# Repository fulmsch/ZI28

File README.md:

# ZI-28: An Expandable Z80 Microcomputer

The ZI-28 is my attempt at developing a Z80 based microcomputer.
The main goals were to have a system that's about as usable as
a personal computer of the 80s and easily expandable with additional hardware.

The project is still very much a work in progress. Both the hardware and the
OS are functional, but many planned features have yet to be implemented.

If you want to try out yourself what using the ZI-28 feels like, you can do so
with the included emulator. See the quick start guide for instructions.

## Prerequisites

It is assumed that you have a standard Linux develompent environment
(gcc, make, etc.) setup already. To build the emulator, you also need Lua 5.3.

The Z80 software requires Z88DK v1.99B in order to be built. Make sure to have
all of the Z88DK binaries in your path. You don't need to worry about the ZCCCFG
environment variable; it gets set automatically by the Makefiles.

The emulator creates a pseudoterminal to simulate the serial connection of the
real computer. To access it, you will need a terminal emulator. For the easiest
experience, picocom should be installed, though you can also use any other one.

## Quick start guide

Ensure that you have all prerequisites installed. Type `make` to build the
entire project. You might be promted for your password to mount the filesystem
image. If the build completed successfully, type `make run`. This will open
the emulator with the newly built ROM- and SD-images and start picocom in your
current terminal window. Click the `continue`-button of the emulator to start
the system.

## Contents of this repository

* **emulator**: Based on libz80 by Gabriel Gambetta, this emulator simulates the
  Z80 processor and all the periphery of the ZI-28. It also includes some
  debugging features.
* **include**: Header files for the C library. These also form the interface to
  the operating system.
* **lib**: Library for compiling C code. Mostly copied from z88dk, but modified
  and expanded for the particularities of the ZI-28.
* **system**: Everything that's part of the machine itself, most notably the
  ROM-based operating system.
* **tools**: Utilities supporting the project.
* **user**: Various programs for the system.

## License

All code original to the ZI-28 project is licensed under the terms of the
GNU General Public License v3.0.

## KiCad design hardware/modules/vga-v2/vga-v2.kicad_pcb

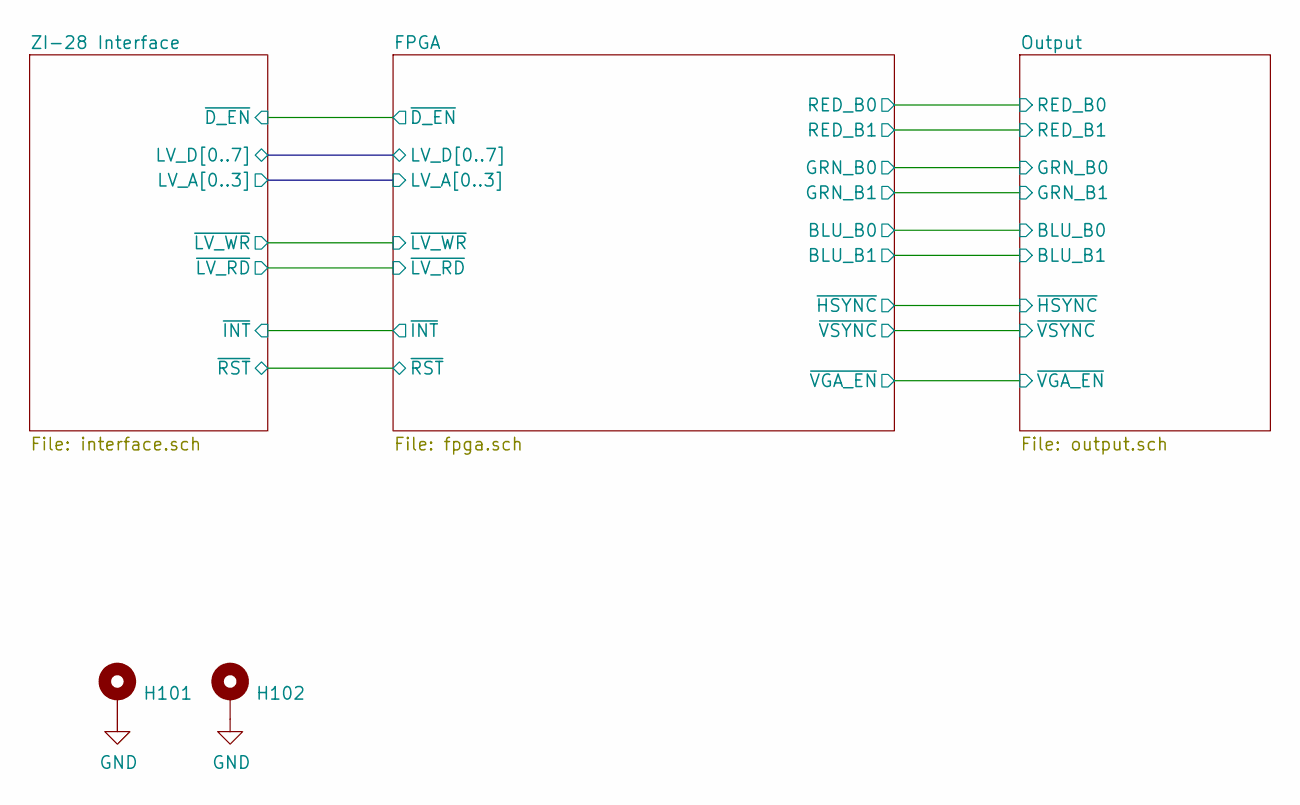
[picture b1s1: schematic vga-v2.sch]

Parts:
H101, H102: MountingHole_Pad; MountingHole_3.2mm_M3_Pad

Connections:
GND: H101.1, H102.1; also elsewhere on the board

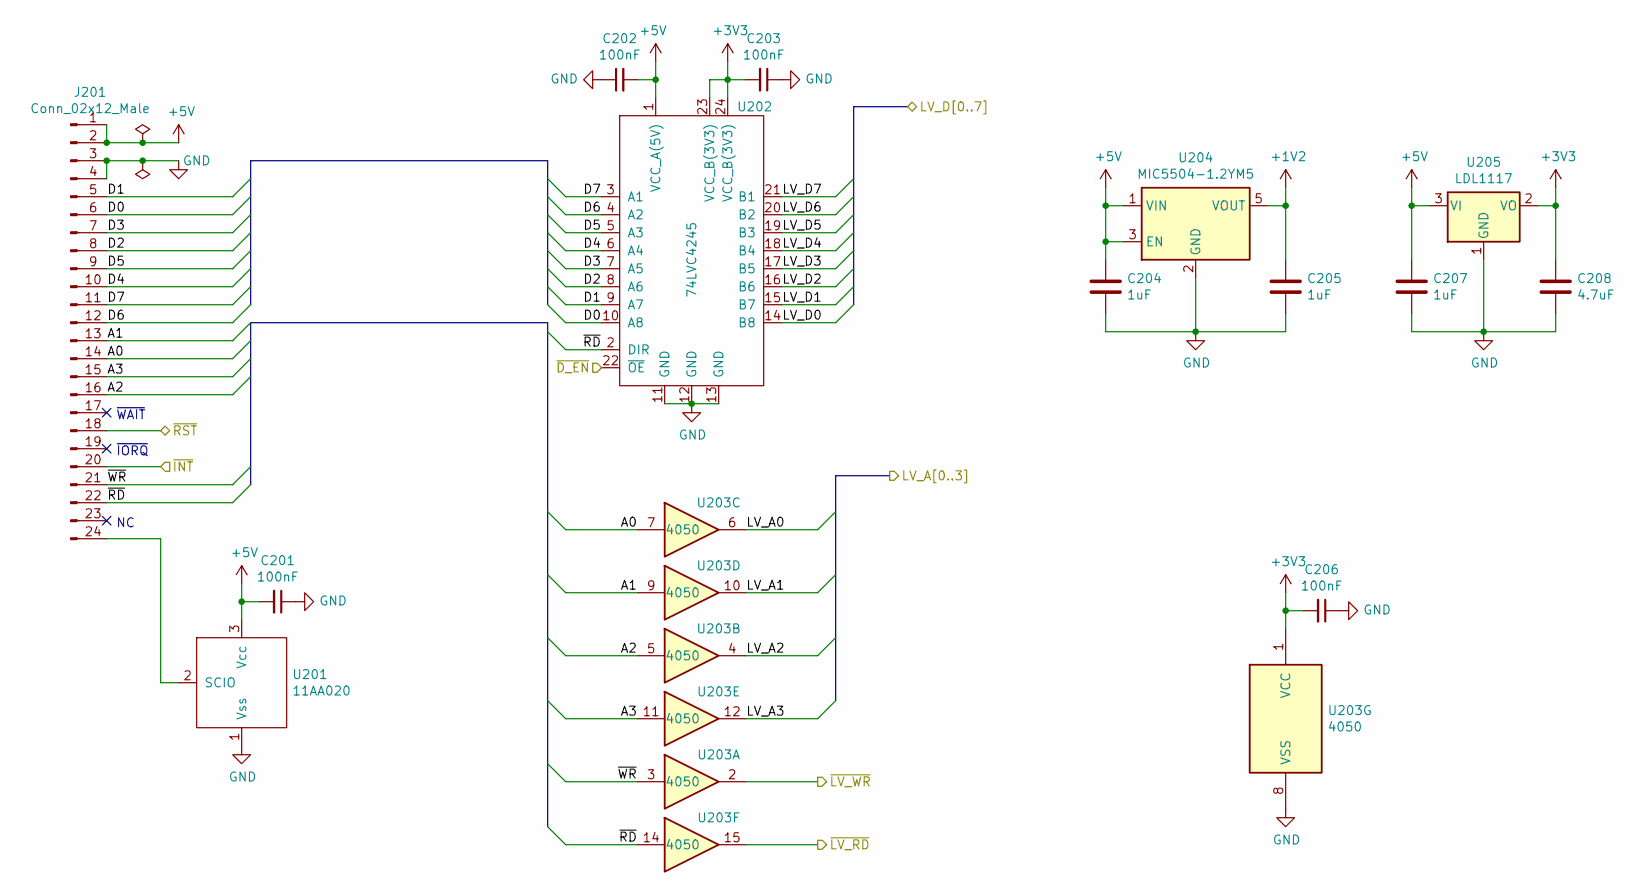
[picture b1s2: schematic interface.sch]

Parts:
C201, C202, C203, C206: 100nF; C_0805_2012Metric_Pad1.15x1.40mm_HandSolder
C204, C205, C207: 1uF; C_0805_2012Metric_Pad1.15x1.40mm_HandSolder
C208: 4.7uF; C_0805_2012Metric_Pad1.15x1.40mm_HandSolder
J201: Conn_02x12_Male; PinHeader_2x12_P2.54mm_Horizontal
U201: 11AA020; TO-92
U202: 74LVC4245; SOIC-24W_7.5x15.4mm_P1.27mm
U203: 4050; SOIC-16W_7.5x10.3mm_P1.27mm
U204: MIC5504-1.2YM5; SOT-23-5
U205: LDL1117; SOT-223-3_TabPin2

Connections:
+1V2: C205.1, U204.5 (VOUT); also elsewhere on the board
+3V3: C203.2, C206.2, C208.1, U202.23 (VCC_B(3V3)), U202.24 (VCC_B(3V3)), U203.1 (VCC), U205.2 (VO); also elsewhere on the board
+5V: C201.2, C202.2, C204.1, C207.1, J201.1, J201.2, U201.3 (Vcc), U202.1 (VCC_A(5V)), U204.1 (VIN), U204.3 (EN), U205.3 (VI)
/FPGA/LV_A0: U203.6; also elsewhere on the board
/FPGA/LV_A1: U203.10; also elsewhere on the board
/FPGA/LV_A2: U203.4; also elsewhere on the board
/FPGA/LV_A3: U203.12; also elsewhere on the board
/FPGA/LV_D0: U202.14 (B8); also elsewhere on the board
/FPGA/LV_D1: U202.15 (B7); also elsewhere on the board
/FPGA/LV_D2: U202.16 (B6); also elsewhere on the board
/FPGA/LV_D3: U202.17 (B5); also elsewhere on the board
/FPGA/LV_D4: U202.18 (B4); also elsewhere on the board
/FPGA/LV_D5: U202.19 (B3); also elsewhere on the board
/FPGA/LV_D6: U202.20 (B2); also elsewhere on the board
/FPGA/LV_D7: U202.21 (B1); also elsewhere on the board
/FPGA/~D_EN: U202.22 (~OE); also elsewhere on the board
/FPGA/~INT: J201.20; also elsewhere on the board
/FPGA/~LV_RD: U203.15; also elsewhere on the board
/FPGA/~LV_WR: U203.2; also elsewhere on the board
/FPGA/~RST: J201.18; also elsewhere on the board
/ZI-28 Interface/A0: J201.14, U203.7
/ZI-28 Interface/A1: J201.13, U203.9
/ZI-28 Interface/A2: J201.16, U203.5
/ZI-28 Interface/A3: J201.15, U203.11
/ZI-28 Interface/D0: J201.6, U202.10 (A8)
/ZI-28 Interface/D1: J201.5, U202.9 (A7)
/ZI-28 Interface/D2: J201.8, U202.8 (A6)
/ZI-28 Interface/D3: J201.7, U202.7 (A5)
/ZI-28 Interface/D4: J201.10, U202.6 (A4)
/ZI-28 Interface/D5: J201.9, U202.5 (A3)
/ZI-28 Interface/D6: J201.12, U202.4 (A2)
/ZI-28 Interface/D7: J201.11, U202.3 (A1)
/ZI-28 Interface/~RD: J201.22, U202.2 (DIR), U203.14
/ZI-28 Interface/~WR: J201.21, U203.3
GND: C201.1, C202.1, C203.1, C204.2, C205.2, C206.1, C207.2, C208.2, J201.3, J201.4, U201.1 (Vss), U202.11 (GND), U202.12 (GND), U202.13 (GND), U203.8 (VSS), U204.2 (GND), U205.1 (GND); also elsewhere on the board
unnamed: J201.24, U201.2 (SCIO)

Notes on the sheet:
~WAIT
~IORQ

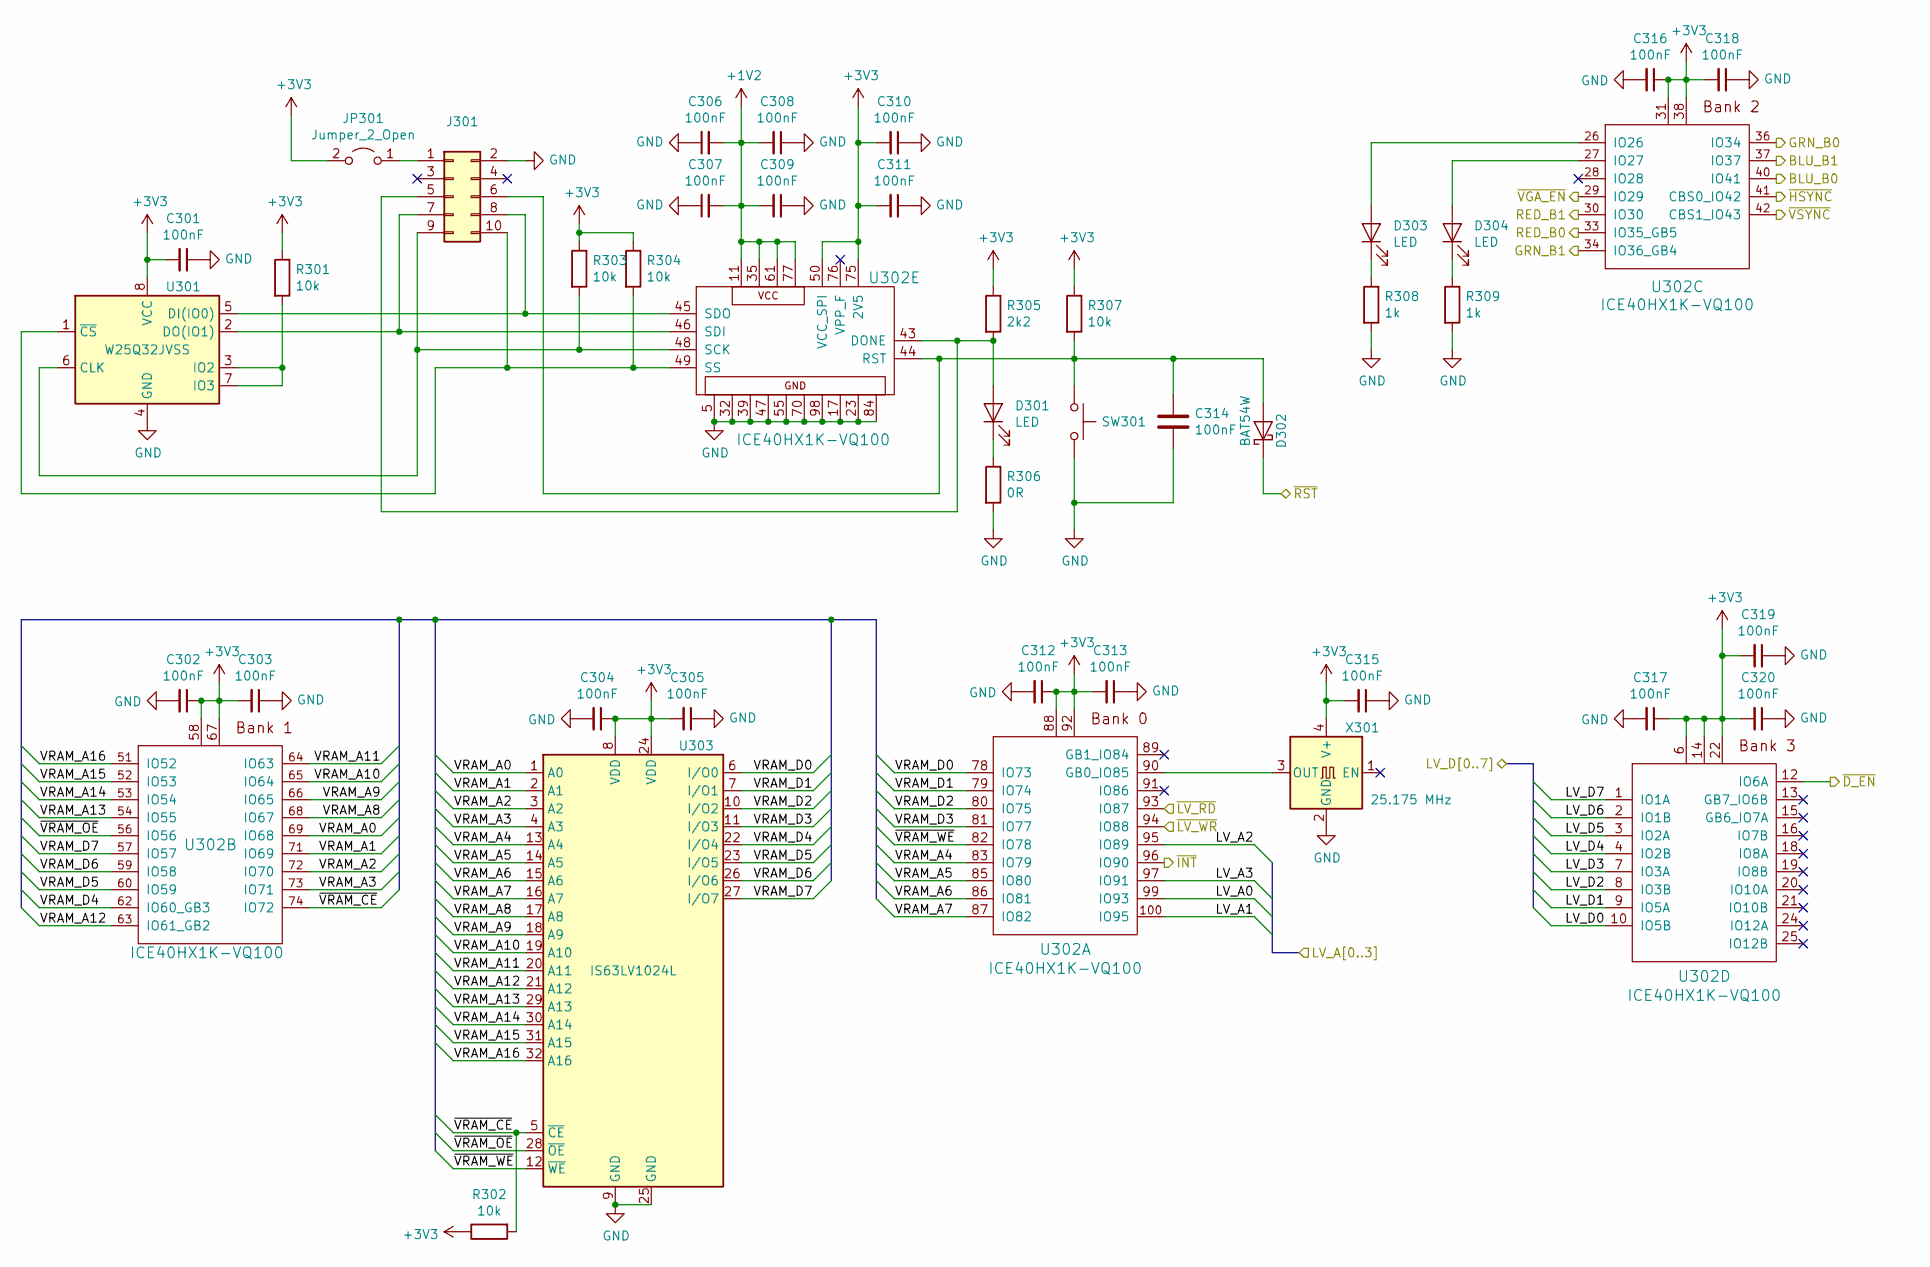
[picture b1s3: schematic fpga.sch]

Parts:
C301, C302, C303, C304, C305, C306, C307, C308, C309, C310, C311, C312, C313, C314, C315, C316, C317, C318, C319, C320: 100nF; C_0805_2012Metric_Pad1.15x1.40mm_HandSolder
D301, D303, D304: LED; LED_D3.0mm
D302: BAT54W; D_SOD-123
J301: Conn_02x05_Odd_Even; IDC-Header_2x05_P2.54mm_Vertical
JP301: Jumper_2_Open; PinHeader_1x02_P2.54mm_Vertical
R301, R302, R303, R304, R307: 10k; R_0805_2012Metric_Pad1.15x1.40mm_HandSolder
R305: 2k2; R_0805_2012Metric_Pad1.15x1.40mm_HandSolder
R306: 0R; R_0805_2012Metric_Pad1.15x1.40mm_HandSolder
R308, R309: 1k; R_0805_2012Metric_Pad1.15x1.40mm_HandSolder
SW301: SW_Push; SW_PUSH_6mm_H5mm
U301: W25Q32JVSS; DIP-8_W7.62mm_Socket
U302: ICE40HX1K-VQ100; VQFP-100_14x14mm_P0.5mm
U303: IS63LV1024L; TSOP-II-32_21.0x10.2mm_P1.27mm
X301: 25.175 MHz; Oscillator_SMD_Abracon_ASV-4Pin_7.0x5.1mm_HandSoldering

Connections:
+1V2: C306.2, C307.2, C308.2, C309.2, U302.11, U302.35, U302.61, U302.77; also elsewhere on the board
+3V3: C301.2, C302.1, C303.2, C304.1, C305.2, C310.2, C311.2, C312.1, C313.2, C315.2, C316.1, C317.1, C318.2, C319.2, C320.2, JP301.2 (B), R301.1, R302.1, R303.1, R304.1, R305.1, R307.1, U301.8 (VCC), U302.6, U302.14, U302.22, U302.31, U302.38, U302.50 (VCC_SPI), U302.58, U302.67, U302.75 (2V5), U302.88, U302.92, U303.8 (VDD), U303.24 (VDD), X301.4 (V+); also elsewhere on the board
/FPGA/BLU_B0: U302.40 (IO41); also elsewhere on the board
/FPGA/BLU_B1: U302.37 (IO37); also elsewhere on the board
/FPGA/GRN_B0: U302.36 (IO34); also elsewhere on the board
/FPGA/GRN_B1: U302.34 (IO36_GB4); also elsewhere on the board
/FPGA/LV_A0: U302.99 (IO93); also elsewhere on the board
/FPGA/LV_A1: U302.100 (IO95); also elsewhere on the board
/FPGA/LV_A2: U302.95 (IO89); also elsewhere on the board
/FPGA/LV_A3: U302.97 (IO91); also elsewhere on the board
/FPGA/LV_D0: U302.10 (IO5B); also elsewhere on the board
/FPGA/LV_D1: U302.9 (IO5A); also elsewhere on the board
/FPGA/LV_D2: U302.8 (IO3B); also elsewhere on the board
/FPGA/LV_D3: U302.7 (IO3A); also elsewhere on the board
/FPGA/LV_D4: U302.4 (IO2B); also elsewhere on the board
/FPGA/LV_D5: U302.3 (IO2A); also elsewhere on the board
/FPGA/LV_D6: U302.2 (IO1B); also elsewhere on the board
/FPGA/LV_D7: U302.1 (IO1A); also elsewhere on the board
/FPGA/RED_B0: U302.33 (IO35_GB5); also elsewhere on the board
/FPGA/RED_B1: U302.30 (IO30); also elsewhere on the board
/FPGA/VRAM_A0: U302.69 (IO68), U303.1 (A0)
/FPGA/VRAM_A1: U302.71 (IO69), U303.2 (A1)
/FPGA/VRAM_A2: U302.72 (IO70), U303.3 (A2)
/FPGA/VRAM_A3: U302.73 (IO71), U303.4 (A3)
/FPGA/VRAM_A4: U302.83 (IO79), U303.13 (A4)
/FPGA/VRAM_A5: U302.85 (IO80), U303.14 (A5)
/FPGA/VRAM_A6: U302.86 (IO81), U303.15 (A6)
/FPGA/VRAM_A7: U302.87 (IO82), U303.16 (A7)
/FPGA/VRAM_A8: U302.68 (IO67), U303.17 (A8)
/FPGA/VRAM_A9: U302.66 (IO65), U303.18 (A9)
/FPGA/VRAM_A10: U302.65 (IO64), U303.19 (A10)
/FPGA/VRAM_A11: U302.64 (IO63), U303.20 (A11)
/FPGA/VRAM_A12: U302.63 (IO61_GB2), U303.21 (A12)
/FPGA/VRAM_A13: U302.54 (IO55), U303.29 (A13)
/FPGA/VRAM_A14: U302.53 (IO54), U303.30 (A14)
/FPGA/VRAM_A15: U302.52 (IO53), U303.31 (A15)
/FPGA/VRAM_A16: U302.51 (IO52), U303.32 (A16)
/FPGA/VRAM_D0: U302.78 (IO73), U303.6 (I/O0)
/FPGA/VRAM_D1: U302.79 (IO74), U303.7 (I/O1)
/FPGA/VRAM_D2: U302.80 (IO75), U303.10 (I/O2)
/FPGA/VRAM_D3: U302.81 (IO77), U303.11 (I/O3)
/FPGA/VRAM_D4: U302.62 (IO60_GB3), U303.22 (I/O4)
/FPGA/VRAM_D5: U302.60 (IO59), U303.23 (I/O5)
/FPGA/VRAM_D6: U302.59 (IO58), U303.26 (I/O6)
/FPGA/VRAM_D7: U302.57 (IO57), U303.27 (I/O7)
/FPGA/~D_EN: U302.12 (IO6A); also elsewhere on the board
/FPGA/~HSYNC: U302.41 (CBS0_IO42); also elsewhere on the board
/FPGA/~INT: U302.96 (IO90); also elsewhere on the board
/FPGA/~LV_RD: U302.93 (IO87); also elsewhere on the board
/FPGA/~LV_WR: U302.94 (IO88); also elsewhere on the board
/FPGA/~RST: D302.1 (K); also elsewhere on the board
/FPGA/~VGA_EN: U302.29 (IO29); also elsewhere on the board
/FPGA/~VRAM_CE: R302.2, U302.74 (IO72), U303.5 (~CE)
/FPGA/~VRAM_OE: U302.56 (IO56), U303.28 (~OE)
/FPGA/~VRAM_WE: U302.82 (IO78), U303.12 (~WE)
/FPGA/~VSYNC: U302.42 (CBS1_IO43); also elsewhere on the board
GND: C301.1, C302.2, C303.1, C304.2, C305.1, C306.1, C307.1, C308.1, C309.1, C310.1, C311.1, C312.2, C313.1, C314.2, C315.1, C316.2, C317.2, C318.1, C319.1, C320.1, J301.2, R306.2, R308.2, R309.2, SW301.2, U301.4 (GND), U302.5, U302.17, U302.23, U302.32, U302.39, U302.47, U302.55, U302.70, U302.84, U302.98, U303.9 (GND), U303.25 (GND), X301.2 (GND); also elsewhere on the board
unnamed: C314.1, D302.2 (A), J301.6, R307.2, SW301.1, U302.44 (RST)
unnamed: D301.1 (K), R306.1
unnamed: D301.2 (A), J301.5, R305.2, U302.43 (DONE)
unnamed: D303.1 (K), R308.1
unnamed: D303.2 (A), U302.26 (IO26)
unnamed: D304.1 (K), R309.1
unnamed: D304.2 (A), U302.27 (IO27)
unnamed: J301.1, JP301.1 (A)
unnamed: J301.7, U301.2 (DO(IO1)), U302.46 (SDI)
unnamed: J301.8, U301.5 (DI(IO0)), U302.45 (SDO)
unnamed: J301.9, R303.2, U301.6 (CLK), U302.48 (SCK)
unnamed: J301.10, R304.2, U301.1 (~CS), U302.49 (SS)
unnamed: R301.2, U301.3 (IO2), U301.7 (IO3)
unnamed: U302.90 (GB0_IO85), X301.3 (OUT)

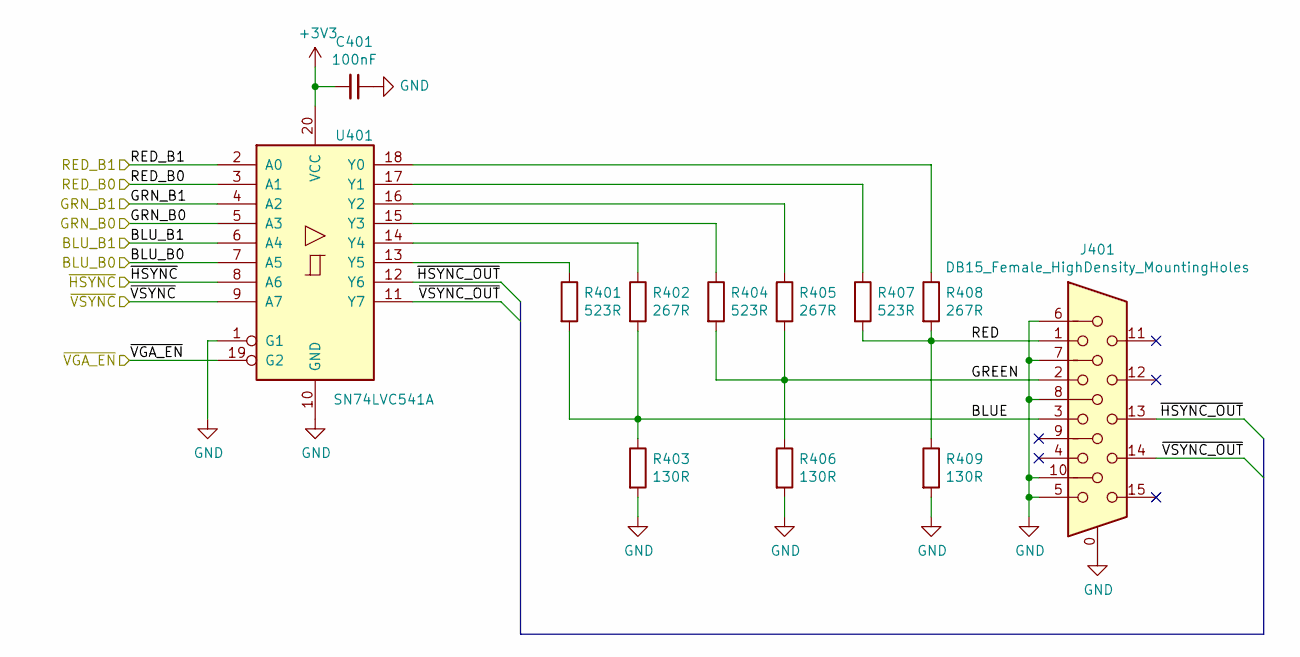
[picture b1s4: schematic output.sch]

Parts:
C401: 100nF; C_0805_2012Metric_Pad1.15x1.40mm_HandSolder
J401: DB15_Female_HighDensity_MountingHoles; DSUB-15-HD_Female_Horizontal_P2.29x1.98mm_EdgePinOffset3.03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
R401, R404, R407: 523R; R_0805_2012Metric_Pad1.15x1.40mm_HandSolder
R402, R405, R408: 267R; R_0805_2012Metric_Pad1.15x1.40mm_HandSolder
R403, R406, R409: 130R; R_0805_2012Metric_Pad1.15x1.40mm_HandSolder
U401: SN74LVC541A; SOIC-20W_7.5x12.8mm_P1.27mm

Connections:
+3V3: C401.2, U401.20 (VCC); also elsewhere on the board
/FPGA/BLU_B0: U401.7 (A5); also elsewhere on the board
/FPGA/BLU_B1: U401.6 (A4); also elsewhere on the board
/FPGA/GRN_B0: U401.5 (A3); also elsewhere on the board
/FPGA/GRN_B1: U401.4 (A2); also elsewhere on the board
/FPGA/RED_B0: U401.3 (A1); also elsewhere on the board
/FPGA/RED_B1: U401.2 (A0); also elsewhere on the board
/FPGA/~HSYNC: U401.8 (A6); also elsewhere on the board
/FPGA/~VGA_EN: U401.19 (G2); also elsewhere on the board
/FPGA/~VSYNC: U401.9 (A7); also elsewhere on the board
/Output/BLUE: J401.3, R401.2, R402.2, R403.1
/Output/GREEN: J401.2, R404.2, R405.2, R406.1
/Output/RED: J401.1, R407.2, R408.2, R409.1
/Output/~HSYNC_OUT: J401.13, U401.12 (Y6)
/Output/~VSYNC_OUT: J401.14, U401.11 (Y7)
GND: C401.1, J401.0, J401.5, J401.6, J401.7, J401.8, J401.10, R403.2, R406.2, R409.2, U401.1 (G1), U401.10 (GND); also elsewhere on the board
unnamed: R401.1, U401.13 (Y5)
unnamed: R402.1, U401.14 (Y4)
unnamed: R404.1, U401.15 (Y3)
unnamed: R405.1, U401.16 (Y2)
unnamed: R407.1, U401.17 (Y1)
unnamed: R408.1, U401.18 (Y0)

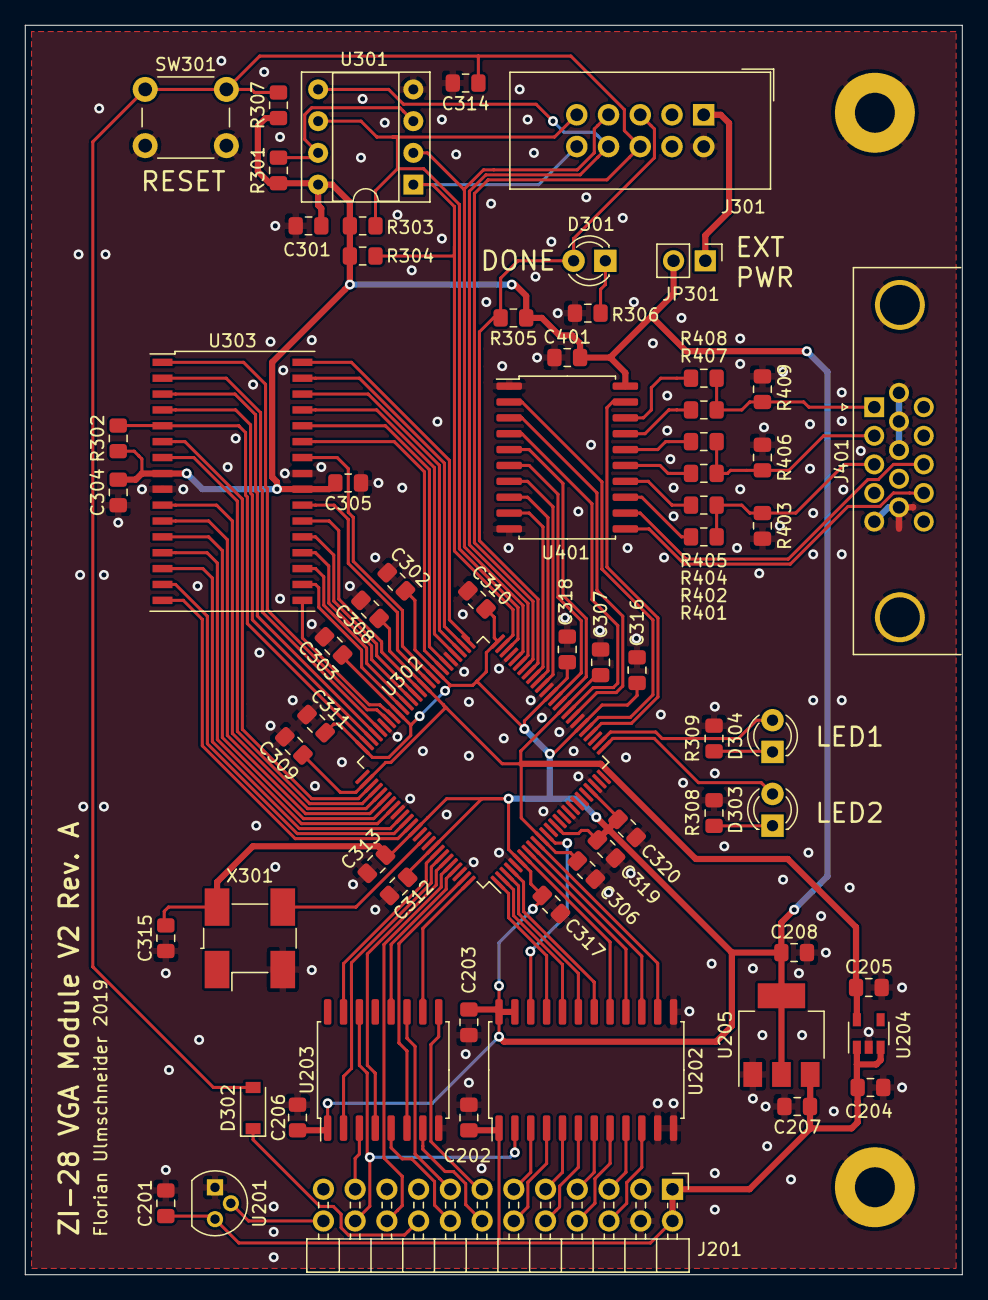
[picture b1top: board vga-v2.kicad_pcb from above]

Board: 2 copper layers, 75.0 x 100.0 mm, 68 parts (0 on the bottom side), 98 nets.

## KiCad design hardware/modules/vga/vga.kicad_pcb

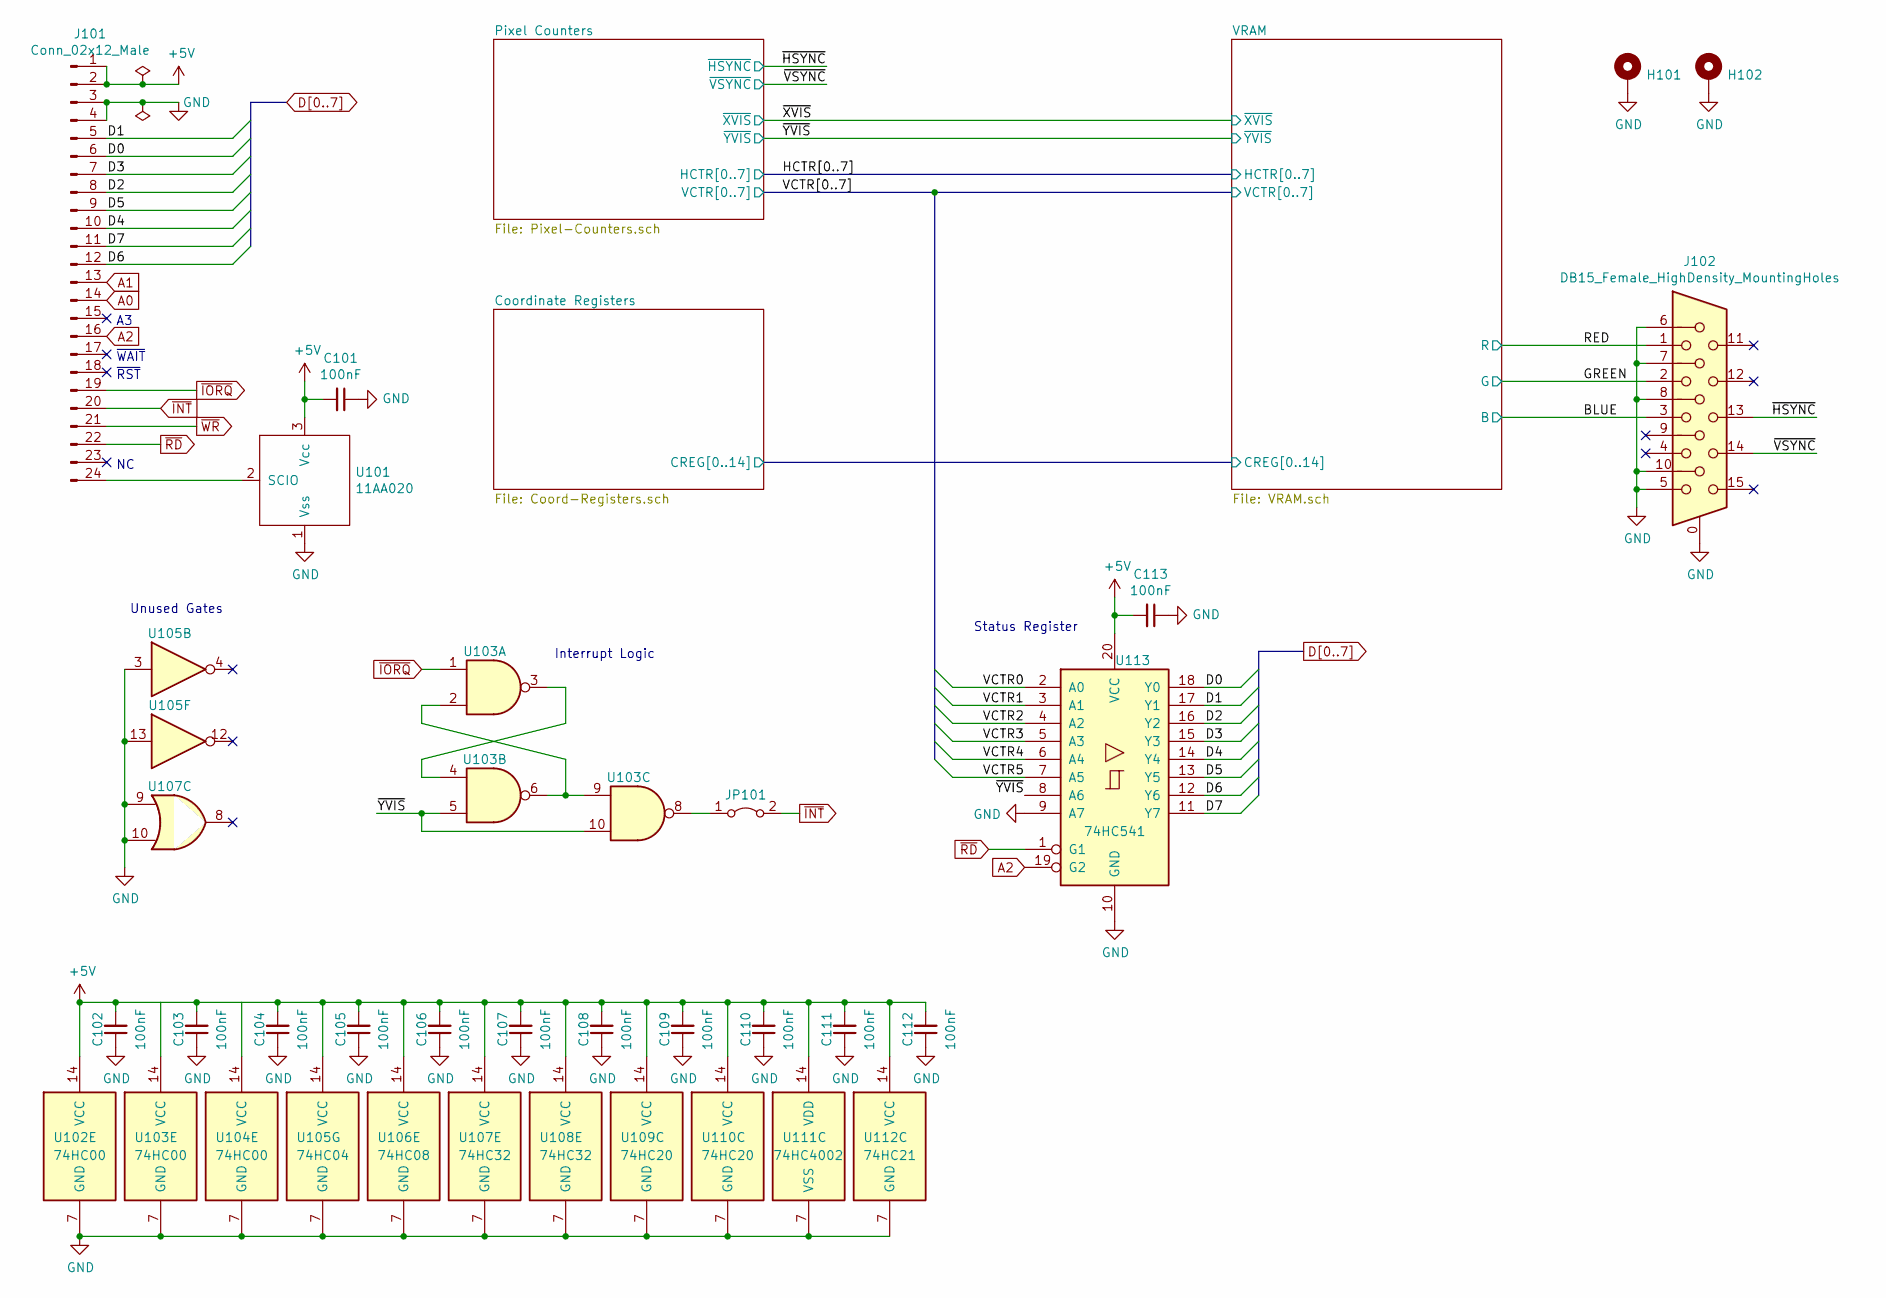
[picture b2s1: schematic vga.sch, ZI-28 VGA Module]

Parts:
C101, C102, C103, C104, C105, C106, C107, C108, C109, C110, C111, C112, C113: 100nF; C_Disc_D3.0mm_W1.6mm_P2.50mm
H101, H102: MountingHole_Pad; MountingHole_3.2mm_M3_Pad
J101: Conn_02x12_Male; PinHeader_2x12_P2.54mm_Horizontal
J102: DB15_Female_HighDensity_MountingHoles; DSUB-15-HD_Female_Horizontal_P2.29x1.98mm_EdgePinOffset3.03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
JP101: Jumper_2_Bridged; PinHeader_1x02_P2.54mm_Vertical
U101: 11AA020; TO-92
U102, U103, U104: 74HC00; DIP-14_W7.62mm_Socket
U105: 74HC04; DIP-14_W7.62mm_Socket
U106: 74HC08; DIP-14_W7.62mm_Socket
U107, U108: 74HC32; DIP-14_W7.62mm_Socket
U109, U110: 74HC20; DIP-14_W7.62mm_Socket
U111: 74HC4002; DIP-14_W7.62mm_Socket
U112: 74HC21; DIP-14_W7.62mm_Socket
U113: 74HC541; DIP-20_W7.62mm_Socket

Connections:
+5V: C101.2, C102.2, C103.2, C104.2, C105.2, C106.2, C107.2, C108.2, C109.2, C110.2, C111.2, C112.2, C113.2, J101.1, J101.2, U101.3 (Vcc), U102.14 (VCC), U103.14 (VCC), U104.14 (VCC), U105.14 (VCC), U106.14 (VCC), U107.14 (VCC), U108.14 (VCC), U109.14 (VCC), U110.14 (VCC), U111.14 (VDD), U112.14 (VCC), U113.20 (VCC); also elsewhere on the board
/BLUE: J102.3; also elsewhere on the board
/GREEN: J102.2; also elsewhere on the board
/RED: J102.1; also elsewhere on the board
/VCTR0: U113.2 (A0); also elsewhere on the board
/VCTR1: U113.3 (A1); also elsewhere on the board
/VCTR2: U113.4 (A2); also elsewhere on the board
/VCTR3: U113.5 (A3); also elsewhere on the board
/VCTR4: U113.6 (A4); also elsewhere on the board
/VCTR5: U113.7 (A5); also elsewhere on the board
/~HSYNC: J102.13; also elsewhere on the board
/~VSYNC: J102.14; also elsewhere on the board
/~YVIS: U103.5, U103.10, U113.8 (A6); also elsewhere on the board
A0: J101.14; also elsewhere on the board
A1: J101.13; also elsewhere on the board
A2: J101.16, U113.19 (G2); also elsewhere on the board
D0: J101.6, U113.18 (Y0); also elsewhere on the board
D1: J101.5, U113.17 (Y1); also elsewhere on the board
D2: J101.8, U113.16 (Y2); also elsewhere on the board
D3: J101.7, U113.15 (Y3); also elsewhere on the board
D4: J101.10, U113.14 (Y4); also elsewhere on the board
D5: J101.9, U113.13 (Y5); also elsewhere on the board
D6: J101.12, U113.12 (Y6); also elsewhere on the board
D7: J101.11, U113.11 (Y7); also elsewhere on the board
GND: C101.1, C102.1, C103.1, C104.1, C105.1, C106.1, C107.1, C108.1, C109.1, C110.1, C111.1, C112.1, C113.1, H101.1, H102.1, J101.3, J101.4, J102.0, J102.5, J102.6, J102.7, J102.8, J102.10, U101.1 (Vss), U102.7 (GND), U103.7 (GND), U104.7 (GND), U105.3, U105.7 (GND), U105.13, U106.7 (GND), U107.7 (GND), U107.9, U107.10, U108.7 (GND), U109.7 (GND), U110.7 (GND), U111.7 (VSS), U112.7 (GND), U113.9 (A7), U113.10 (GND); also elsewhere on the board
unnamed: J101.24, U101.2 (SCIO)
unnamed: JP101.1 (A), U103.8
unnamed: U103.2, U103.6, U103.9
unnamed: U103.3, U103.4
~INT: J101.20, JP101.2 (B)
~IORQ: J101.19, U103.1; also elsewhere on the board
~RD: J101.22, U113.1 (G1)
~WR: J101.21; also elsewhere on the board

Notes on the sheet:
Status Register
Interrupt Logic
~WAIT
~RST
Unused Gates

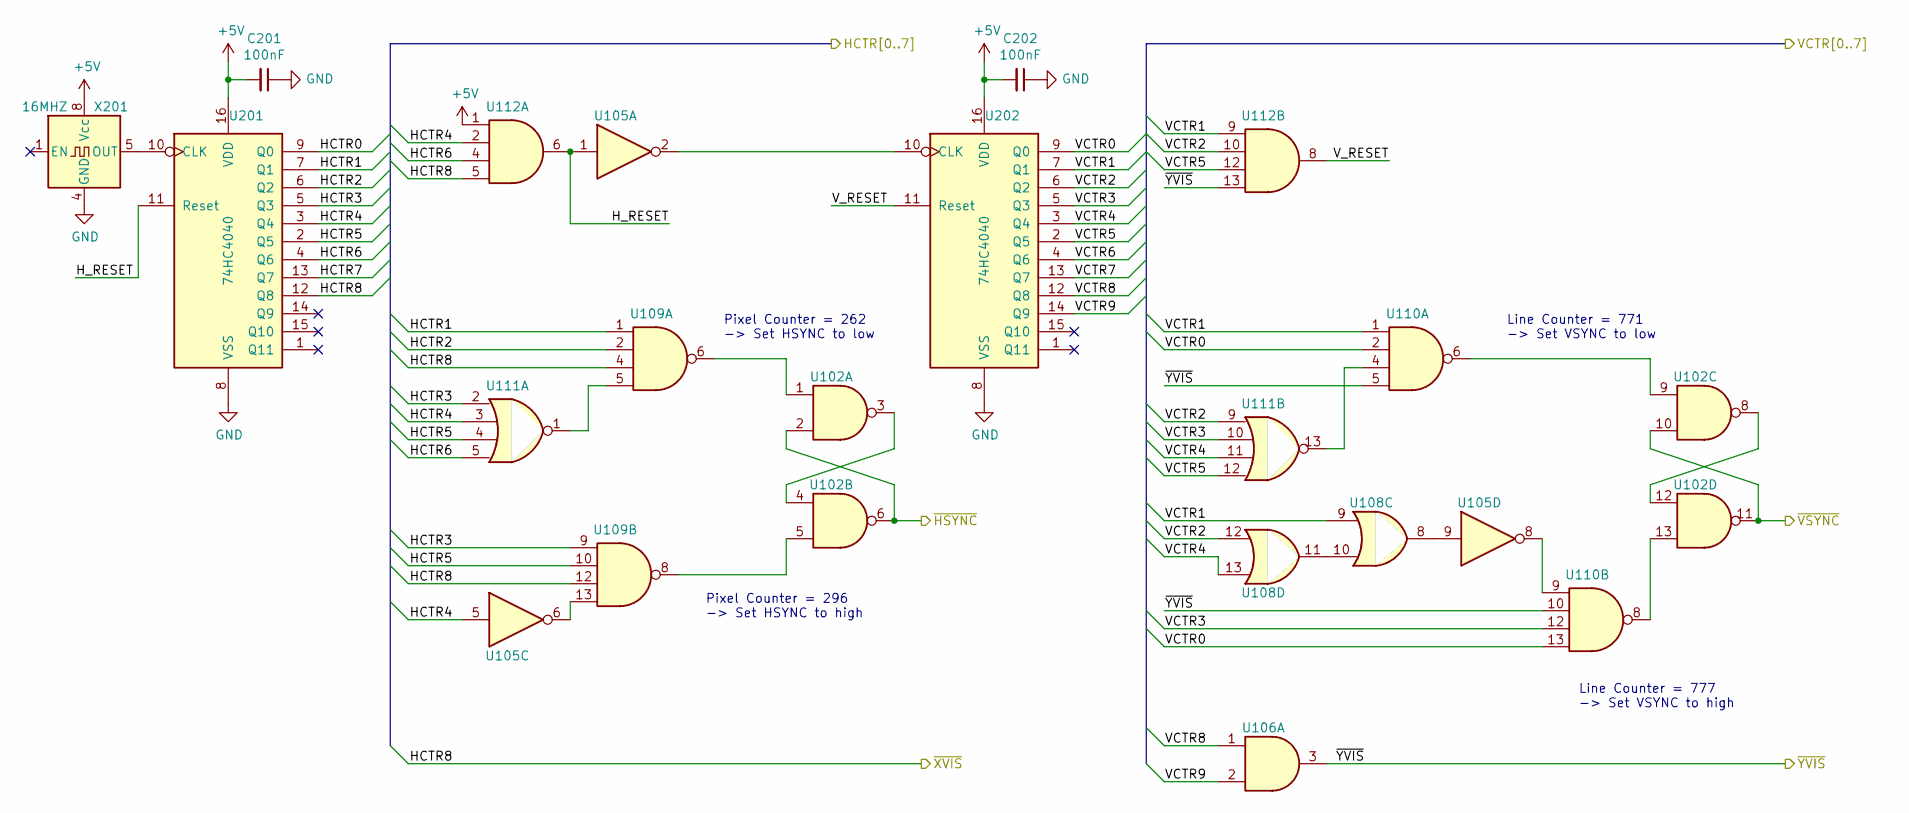
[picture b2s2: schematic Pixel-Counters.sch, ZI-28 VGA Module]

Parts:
C201, C202: 100nF; C_Disc_D3.0mm_W1.6mm_P2.50mm
U102: 74HC00; DIP-14_W7.62mm_Socket
U105: 74HC04; DIP-14_W7.62mm_Socket
U106: 74HC08; DIP-14_W7.62mm_Socket
U108: 74HC32; DIP-14_W7.62mm_Socket
U109, U110: 74HC20; DIP-14_W7.62mm_Socket
U111: 74HC4002; DIP-14_W7.62mm_Socket
U112: 74HC21; DIP-14_W7.62mm_Socket
U201, U202: 74HC4040; DIP-16_W7.62mm_Socket
X201: 16MHZ; DIP-8_W7.62mm_Socket

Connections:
+5V: C201.2, C202.2, U112.1, U201.16 (VDD), U202.16 (VDD), X201.8 (Vcc); also elsewhere on the board
/Pixel Counters/HCTR0: U201.9 (Q0); also elsewhere on the board
/Pixel Counters/HCTR1: U109.1, U201.7 (Q1); also elsewhere on the board
/Pixel Counters/HCTR2: U109.2, U201.6 (Q2); also elsewhere on the board
/Pixel Counters/HCTR3: U109.9, U111.2, U201.5 (Q3); also elsewhere on the board
/Pixel Counters/HCTR4: U105.5, U111.3, U112.2, U201.3 (Q4); also elsewhere on the board
/Pixel Counters/HCTR5: U109.10, U111.4, U201.2 (Q5); also elsewhere on the board
/Pixel Counters/HCTR6: U111.5, U112.4, U201.4 (Q6); also elsewhere on the board
/Pixel Counters/HCTR7: U201.13 (Q7); also elsewhere on the board
/Pixel Counters/H_RESET: U105.1, U112.6, U201.11 (Reset)
/Pixel Counters/VCTR6: U202.4 (Q6); also elsewhere on the board
/Pixel Counters/VCTR7: U202.13 (Q7); also elsewhere on the board
/Pixel Counters/VCTR8: U106.1, U202.12 (Q8)
/Pixel Counters/VCTR9: U106.2, U202.14 (Q9)
/Pixel Counters/V_RESET: U112.8, U202.11 (Reset)
/VCTR0: U110.2, U110.13, U202.9 (Q0); also elsewhere on the board
/VCTR1: U108.9, U110.1, U112.9, U202.7 (Q1); also elsewhere on the board
/VCTR2: U108.12, U111.9, U112.10, U202.6 (Q2); also elsewhere on the board
/VCTR3: U110.12, U111.10, U202.5 (Q3); also elsewhere on the board
/VCTR4: U108.13, U111.11, U202.3 (Q4); also elsewhere on the board
/VCTR5: U111.12, U112.12, U202.2 (Q5); also elsewhere on the board
/~HSYNC: U102.2, U102.6; also elsewhere on the board
/~VSYNC: U102.10, U102.11; also elsewhere on the board
/~XVIS: U109.4, U109.12, U112.5, U201.12 (Q8); also elsewhere on the board
/~YVIS: U106.3, U110.5, U110.10, U112.13; also elsewhere on the board
GND: C201.1, C202.1, U201.8 (VSS), U202.8 (VSS), X201.4 (GND); also elsewhere on the board
unnamed: U102.1, U109.6
unnamed: U102.3, U102.4
unnamed: U102.5, U109.8
unnamed: U102.9, U110.6
unnamed: U102.8, U102.12
unnamed: U102.13, U110.8
unnamed: U105.2, U202.10 (CLK)
unnamed: U105.6, U109.13
unnamed: U105.8, U110.9
unnamed: U105.9, U108.8
unnamed: U108.10, U108.11
unnamed: U109.5, U111.1
unnamed: U110.4, U111.13
unnamed: U201.10 (CLK), X201.5 (OUT)

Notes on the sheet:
Pixel Counter = 296 -> Set HSYNC to high
Pixel Counter = 262 -> Set HSYNC to low
Line Counter = 771 -> Set VSYNC to low
Line Counter = 777 -> Set VSYNC to high
